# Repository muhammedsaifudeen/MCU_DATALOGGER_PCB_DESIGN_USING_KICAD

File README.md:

# 📊 ATmega328P Data Logger with EEPROM and RTC

A low-power, offline data logger built using the **ATmega328P** microcontroller. It logs sensor data to a 512KB external I2C EEPROM, timestamped using a DS3231 RTC. Ideal for **environmental monitoring**, **industrial logging**, or **DIY electronics** where low power and reliability matter.

---

## 🖼️ Assembled Hardware

---

## 🔧 Features

- ✅ Microcontroller: **ATmega328P @ 16 MHz**
- 📦 Memory: **512KB External EEPROM (24LC512)**
- 🕒 Timekeeping: **DS3231 Real-Time Clock**
- 📝 Data Logging: Accurate timestamps with each entry
- 🔌 Interfaces: **I2C** (EEPROM & RTC), **UART** (debug/data dump)
- 💾 Power Efficient: Sleep modes supported
- 🔄 Circular or sequential EEPROM writing (configurable)
- 📠 UART Command Interface:
  - `LOG` – Start logging
  - `DUMP` – Dump stored data
  - `CLR` – Clear EEPROM

---

## 🛠️ Hardware Used

| Component      | Description                      |
|----------------|----------------------------------|
| ATmega328P     | 8-bit AVR microcontroller         |
| 24LC512        | 512KB I2C EEPROM                  |
| DS3231         | Real-Time Clock Module            |
| 16 MHz Crystal | External oscillator for MCU       |
| 22pF Capacitors| For crystal stabilization         |
| 100nF Capacitors | Decoupling for VCC              |
| I2C Pull-ups   | 4.7k–10kΩ on SDA/SCL              |
| UART Header    | For serial interface              |
| Power Supply   | 5V regulated                      |

---

## 🧑‍💻 Firmware Features

- Written in C using **AVR-GCC** and **AVR Libc**
- I2C Master driver for EEPROM and RTC
- UART command interface with interrupt-driven RX
- Optional EEPROM wear-leveling logic
- Time/date initialization via UART or hardcoded config
- Supports both **circular** and **linear logging modes**

---

## 📂 Project Folder Structure

.
├── src/
│ ├── main.c
│ ├── rtc.c / rtc.h
│ ├── eeprom.c / eeprom.h
│ ├── uart.c / uart.h
│ └── utils.c / utils.h
├── include/
├── schematics/
│ ├── datalogger_board.png <- Board photo
│ └── datalogger_schematic.pdf <- Full circuit diagram
├── Makefile
└── README.md

---

## 📐 Schematics

-  

---

## 🚀 Usage (UART Commands)

Once flashed and running, use a UART terminal (e.g., PuTTY, Minicom):

| Command | Function               |
|---------|------------------------|
| `LOG`   | Start data logging     |
| `DUMP`  | Print all stored logs  |
| `CLR`   | Clear EEPROM memory    |

---

## ⚡ Power Modes

- Uses **AVR sleep modes** between logging intervals
- Ideal for **battery-powered deployments**

---

## 🧩 Future Ideas

- Add SD card support for long-term storage  
- Add sensors (e.g., DHT22, BMP280) via I2C  
- Enable wireless sync via BLE or ESP8266  

---

## 📜 License

This project is open-source under the **MIT License**. See `LICENSE` file for details.

---

## 👨‍💻 Author

**Muhammed S**  
[GitHub](https://github.com/muhammedsaifudeen) • Embedded Systems Developer

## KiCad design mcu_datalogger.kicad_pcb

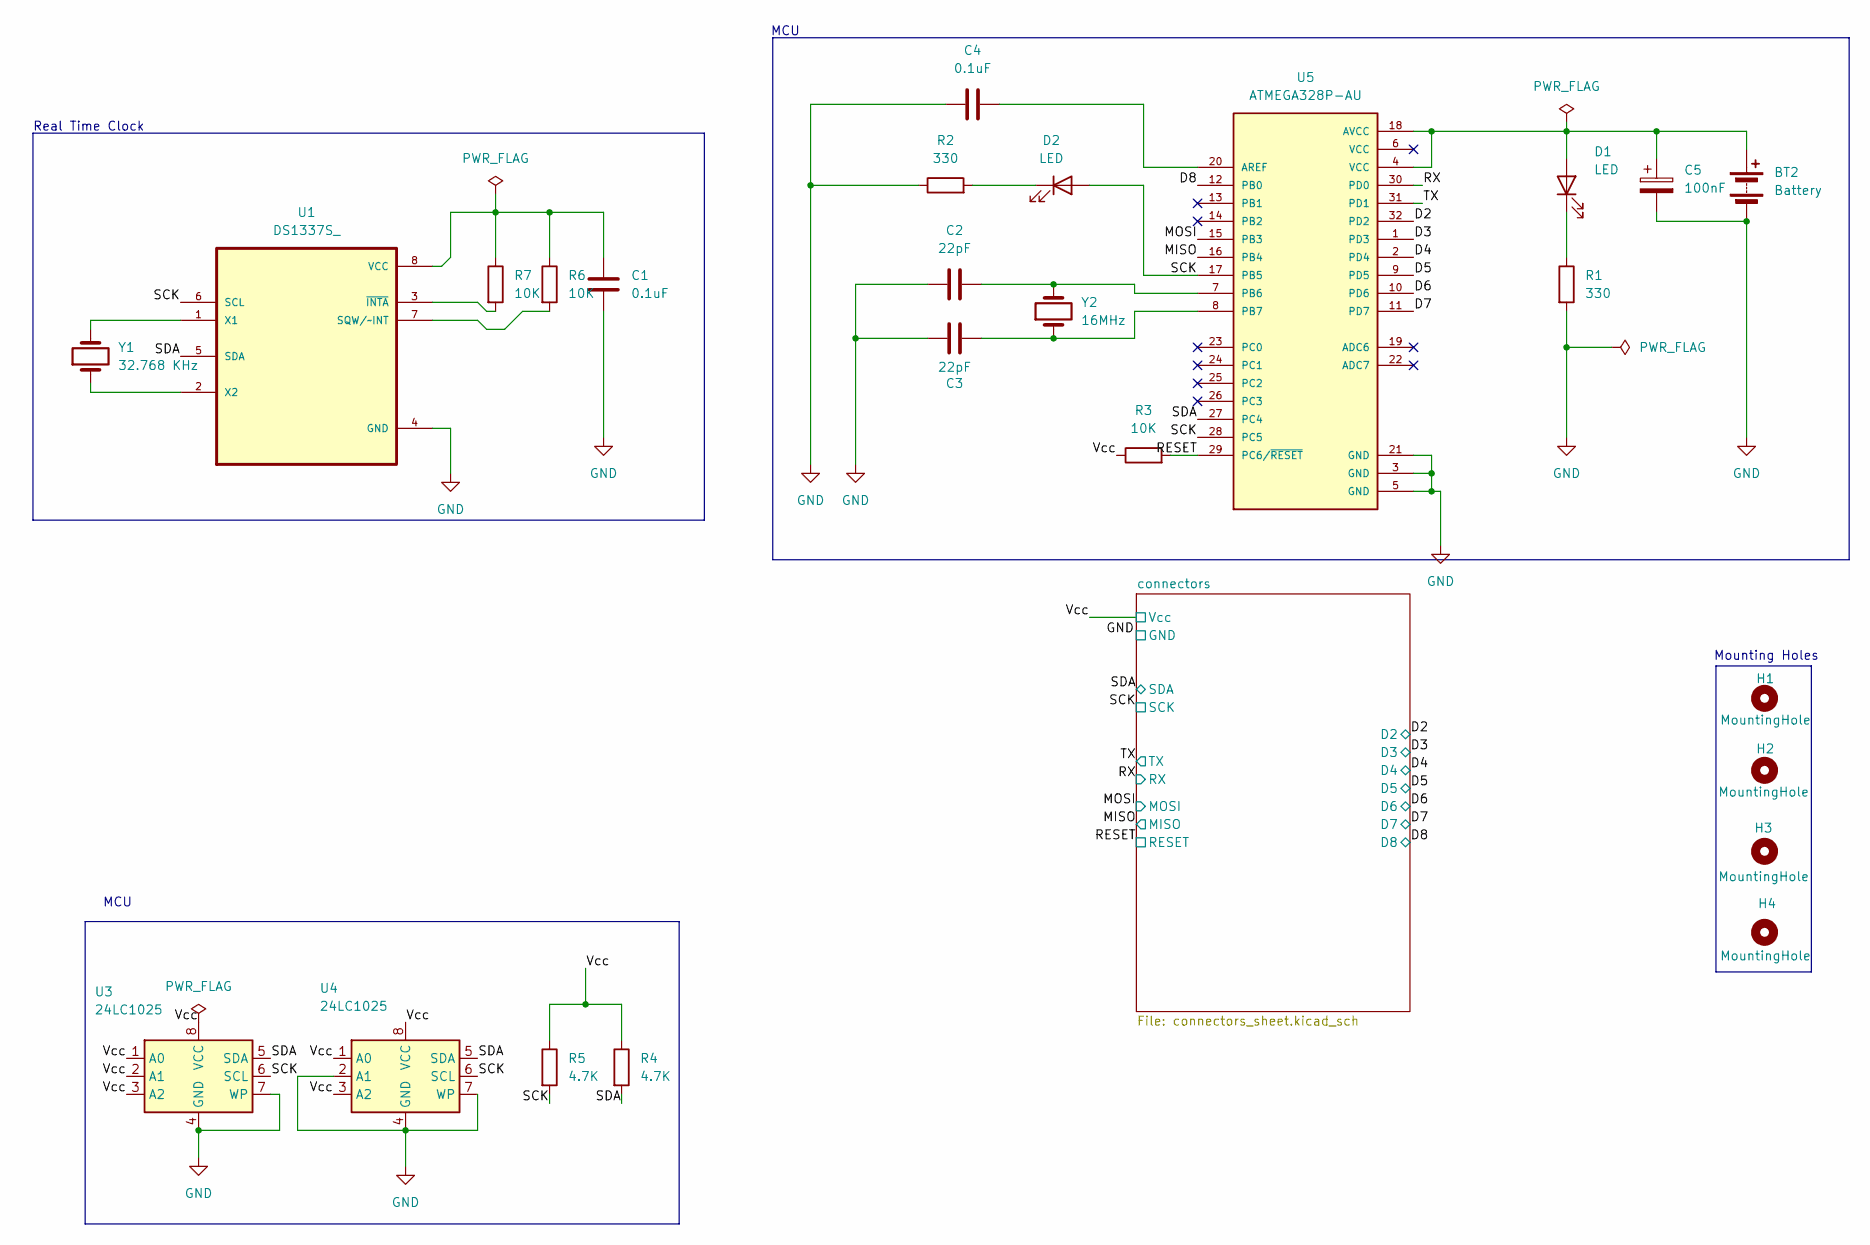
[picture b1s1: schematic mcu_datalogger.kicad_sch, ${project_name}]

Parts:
BT2: Battery; PinHeader_1x02_P2.54mm_Vertical
C1, C4: 0.1uF; C_0805_2012Metric
C2, C3: 22pF; C_0805_2012Metric
C5: 100nF; LED_0805_2012Metric
D1, D2: LED; LED_0805_2012Metric
H1, H2, H3, H4: MountingHole; MountingHole_2.1mm
R1, R2: 330; R_0805_2012Metric
R3, R6, R7: 10K; R_0805_2012Metric
R4, R5: 4.7K; R_0805_2012Metric
U1: DS1337S_; DS1337
U3, U4: 24LC1025; SOIC-8_5.23x5.23mm_P1.27mm
U5: ATMEGA328P-AU; QFP80P900X900X120-32N; PARTREV 8271A
Y1: 32.768 KHz; Crystal_SMD_5032-2Pin_5.0x3.2mm_HandSoldering
Y2: 16MHz; Crystal_SMD_5032-2Pin_5.0x3.2mm_HandSoldering

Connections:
/AVCC: BT2.1 (+), C5.1, D1.2 (A), U5.4 (VCC), U5.18 (AVCC)
/D2: U5.32 (PD2); also elsewhere on the board
/D3: U5.1 (PD3); also elsewhere on the board
/D4: U5.2 (PD4); also elsewhere on the board
/D5: U5.9 (PD5); also elsewhere on the board
/D6: U5.10 (PD6); also elsewhere on the board
/D7: U5.11 (PD7); also elsewhere on the board
/D8: U5.12 (PB0); also elsewhere on the board
/MISO: U5.16 (PB4); also elsewhere on the board
/MOSI: U5.15 (PB3); also elsewhere on the board
/R1_1: D1.1 (K), R1.1
/RESET: R3.2, U5.29 (PC6/~RESET); also elsewhere on the board
/RX: U5.30 (PD0); also elsewhere on the board
/SCK: D2.2 (A), R5.2, U1.6 (SCL), U3.6 (SCL), U4.6 (SCL), U5.17 (PB5), U5.28 (PC5); also elsewhere on the board
/SDA: R4.2, U1.5 (SDA), U3.5 (SDA), U4.5 (SDA), U5.27 (PC4); also elsewhere on the board
/TX: U5.31 (PD1); also elsewhere on the board
/Vcc: R3.1, R4.1, R5.1, U3.1 (A0), U3.2 (A1), U3.3 (A2), U3.8 (VCC), U4.1 (A0), U4.3 (A2), U4.8 (VCC); also elsewhere on the board
/X1: U1.1 (X1), Y1.2
/X2: U1.2 (X2), Y1.1
GND: BT2.2 (-), C1.2, C2.1, C3.1, C4.1, C5.2, R1.2, R2.1, U1.4 (GND), U3.4 (GND), U3.7 (WP), U4.2 (A1), U4.4 (GND), U4.7 (WP), U5.3 (GND), U5.5 (GND), U5.21 (GND); also elsewhere on the board
unnamed: D2.1 (K), R2.2
unnamed: R6.2, U1.7 (SQW/~INT)
unnamed: C1.1, R6.1, R7.1, U1.8 (VCC)
unnamed: R7.2, U1.3 (~INTA)
unnamed: C4.2, U5.20 (AREF)
unnamed: C2.2, U5.7 (PB6), Y2.2
unnamed: C3.2, U5.8 (PB7), Y2.1

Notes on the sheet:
Real Time Clock
MCU
Mounting Holes

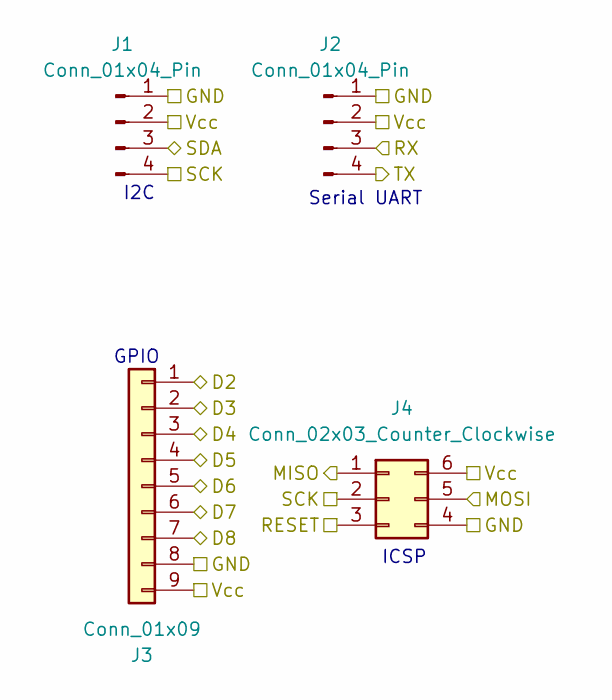
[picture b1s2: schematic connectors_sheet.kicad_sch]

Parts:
J1, J2: Conn_01x04_Pin; PinHeader_1x04_P2.54mm_Vertical
J3: Conn_01x09; PinHeader_1x09_P2.54mm_Vertical
J4: Conn_02x03_Counter_Clockwise; PinHeader_2x03_P2.54mm_Vertical

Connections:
/D2: J3.1; also elsewhere on the board
/D3: J3.2; also elsewhere on the board
/D4: J3.3; also elsewhere on the board
/D5: J3.4; also elsewhere on the board
/D6: J3.5; also elsewhere on the board
/D7: J3.6; also elsewhere on the board
/D8: J3.7; also elsewhere on the board
/MISO: J4.1; also elsewhere on the board
/MOSI: J4.5; also elsewhere on the board
/RESET: J4.3; also elsewhere on the board
/RX: J2.3; also elsewhere on the board
/SCK: J1.4, J4.2; also elsewhere on the board
/SDA: J1.3; also elsewhere on the board
/TX: J2.4; also elsewhere on the board
/Vcc: J1.2, J2.2, J3.9, J4.6; also elsewhere on the board
GND: J1.1, J2.1, J3.8, J4.4; also elsewhere on the board

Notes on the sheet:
GPIO
Serial UART
I2C
ICSP

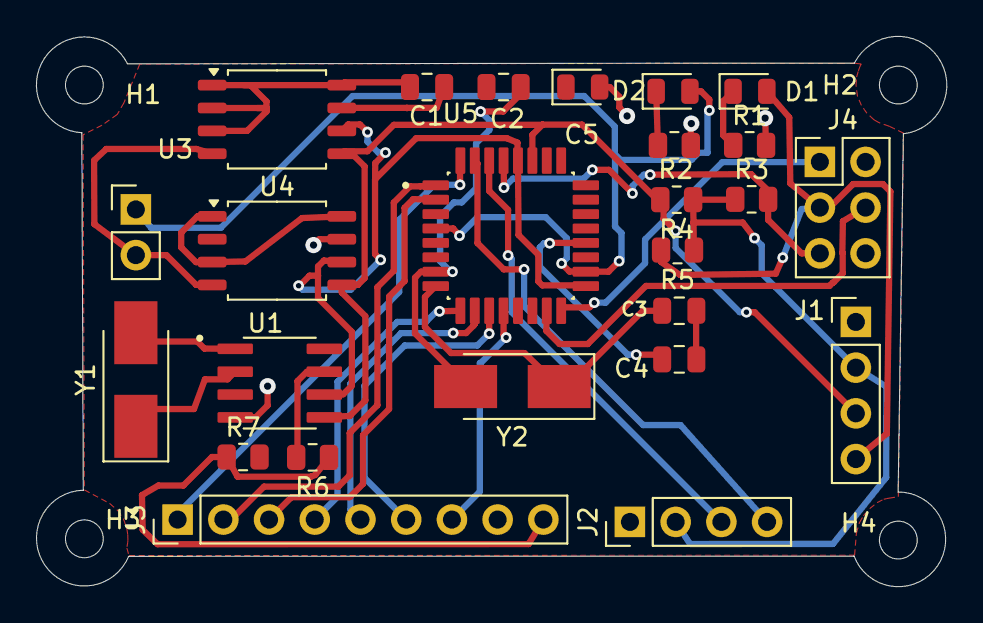
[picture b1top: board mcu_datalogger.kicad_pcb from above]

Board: 2 copper layers, 50.6 x 30.6 mm, 29 parts (0 on the bottom side), 27 nets.

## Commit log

2025-03-16 First Commit of the Project.
2025-03-16 Setup of EESchema for new project
2025-03-16 Added symbols in 2 sheets
2025-03-16 Changed locations of symbols
2025-03-16 Added Component Values
2025-03-16 Updated the Footprint
2025-03-17 Saved necessary files
2025-03-17 Complted the wiring of main sheet
2025-03-19 Added Pin diagram to the Connector
2025-03-19 Added Net (Vcc and GND to the power net)
2025-03-19 Schematic Diagram connections are added
2025-03-19 Added Text &Marking for Easy understanding
2025-03-19 Added all the Markings for Mounting Hole
2025-04-06 Added PCB and Netlist(Power) as GND&VCC
2025-04-06 PCB Layout Started
2025-04-07 PCB Layout Updated
2025-04-09 Layout almost completed
2025-04-11 Added the Zones for GND & VCC
2025-06-02 Added 3D images of PCB via upload
2025-07-10 Update README with board image
2025-07-10 Add board hardware image and update README
2025-07-10 Add schematic image to readme and to the images folder
